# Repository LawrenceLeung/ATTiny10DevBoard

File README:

ATTiny10 in UDFN-6 dev board and HV programmer adapter for ICSP programmer

Designed for single layer etch process

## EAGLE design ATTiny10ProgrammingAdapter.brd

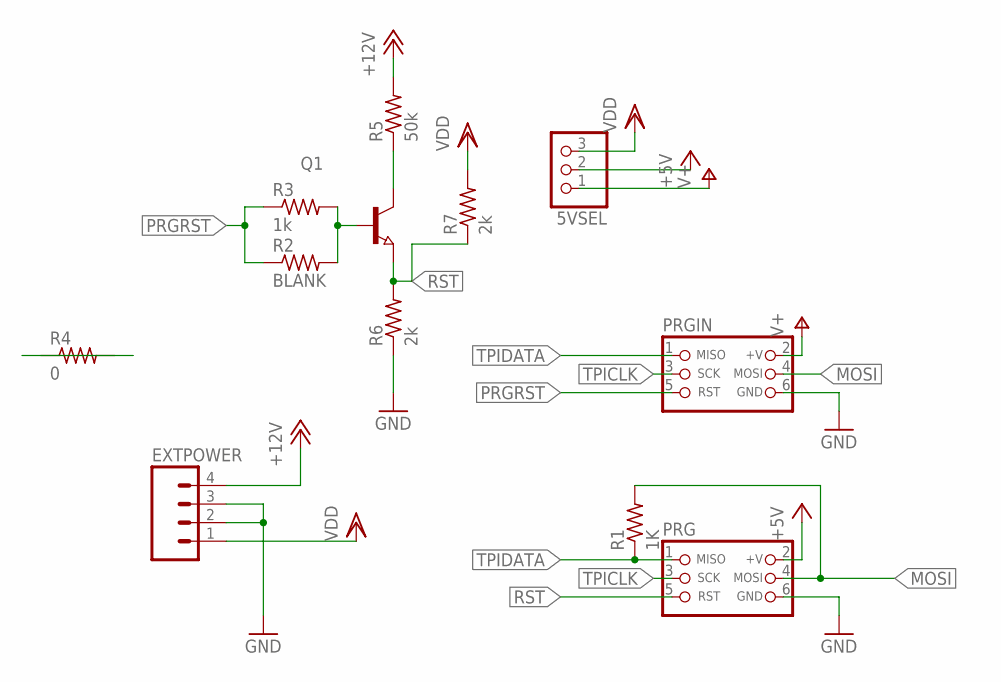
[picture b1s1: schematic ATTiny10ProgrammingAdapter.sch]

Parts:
5VSEL: PINHD-1X3CB; 1X03-CLEANBIG
EXTPOWER: HEADER1X4SMD_LONGPADS; 1X04-SMD-LONG
PRG: CON_HEADER_PRG_AVR_ICSP_ETCH; HEADER_PRG_2X03_ETCH
PRGIN: CON_HEADER_PRG_AVR_ICSP_ETCH; HEADER_PRG_2X03_ETCH
Q1: NPN-TRANSISTOR_SOT23; SOT23
R1: 1K; R0805
R2: BLANK; R0805
R3: 1k; R0805
R4: 0; R1206
R5: 50k; R0805
R6, R7: 2k; R0805

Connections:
+5V: 5VSEL.2, PRG.2 (+V)
+12V: EXTPOWER.4, R4.1, R4.2, R5.2
GND: EXTPOWER.2, EXTPOWER.3, PRG.6 (GND), PRGIN.6 (GND), R6.1
MOSI: PRG.4 (MOSI), PRGIN.4 (MOSI), R1.2
unnamed: Q1.1 (B), R2.2, R3.2
unnamed: Q1.3 (C), R5.1
PRGRST: PRGIN.5 (RST), R2.1, R3.1
RST: PRG.5 (RST), Q1.2 (E), R6.2, R7.1
TPICLK: PRG.3 (SCK), PRGIN.3 (SCK)
TPIDATA: PRG.1 (MISO), PRGIN.1 (MISO), R1.1
V+: 5VSEL.1, PRGIN.2 (+V)
VDD: 5VSEL.3, EXTPOWER.1, R7.2

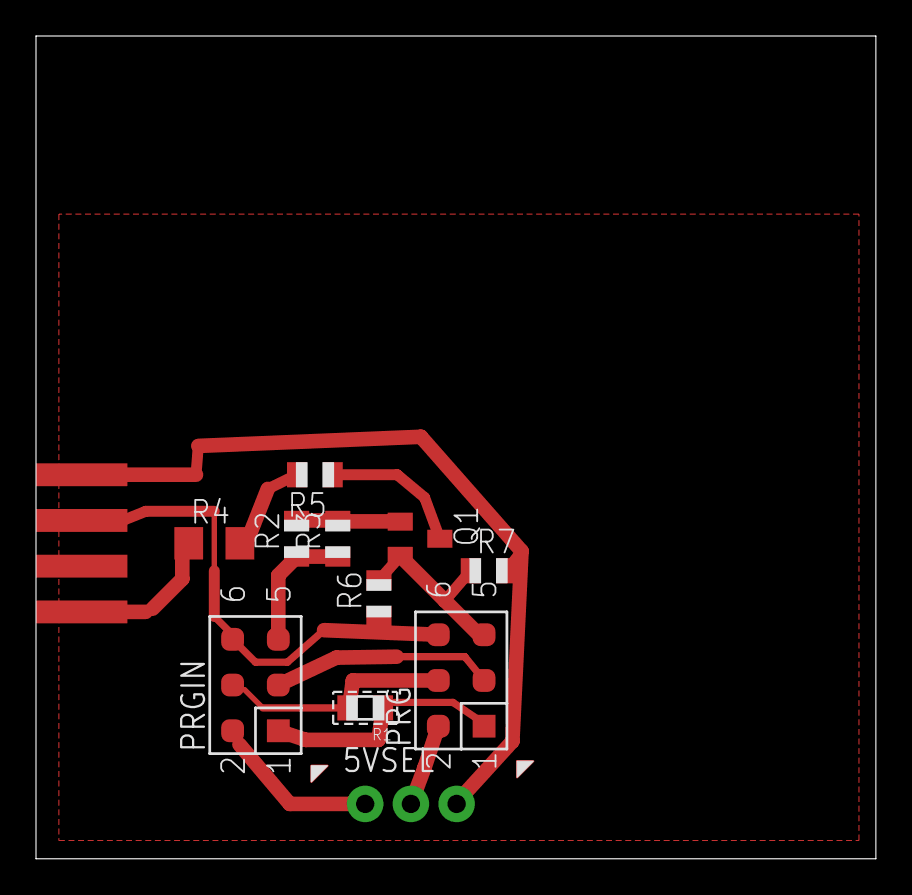
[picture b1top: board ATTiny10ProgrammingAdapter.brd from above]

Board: 2 copper layers, 46.7 x 45.7 mm, 12 parts (0 on the bottom side), 12 nets.

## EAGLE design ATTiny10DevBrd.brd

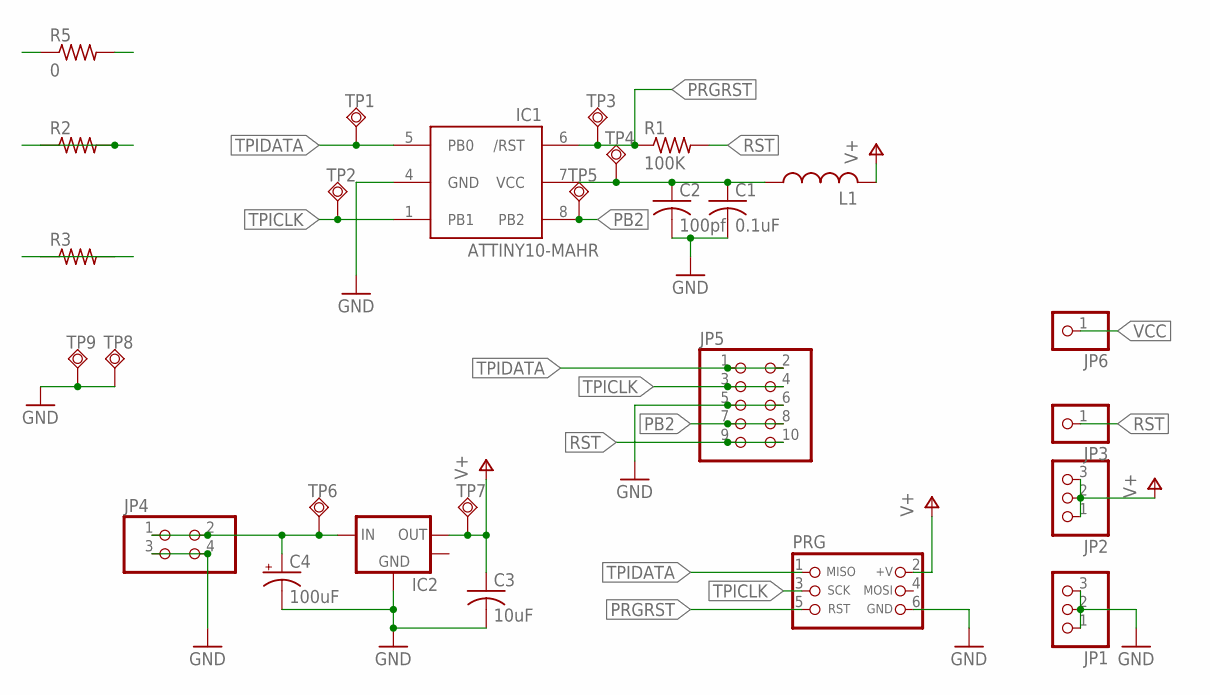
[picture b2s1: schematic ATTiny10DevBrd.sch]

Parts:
C1: 0.1uF; C0603
C2: 100pf; C0402
C3: 10uF; C0805K
C4: 100uF; PANASONIC_E
IC1: ATTINY10-MAHR; UDFN-8
IC2: V_REG_LM1117SOT223; SOT223
JP1, JP2: PINHD-1X3; 1X03
JP3, JP6: PINHD-1X1; 1X01
JP4: PINHD-2X2; 2X02
JP5: PINHD-2X5; 2X05
L1: L-USL1812; L1812
PRG: CON_HEADER_PRG_AVR_ICSP_ETCH; HEADER_PRG_2X03_ETCH
R1: 100K; R0805
R2, R3: R-US_M1206; M1206
R5: 0; M0805
TP1, TP2, TP3, TP4, TP5, TP6, TP7, TP8, TP9: TPSQTP12R; TP12R

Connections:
GND: C1.2, C2.2, C3.2, C4.-, IC1.4 (GND), IC2.1 (GND), JP1.1, JP1.2, JP1.3, JP4.3, JP4.4, JP5.5, JP5.6, PRG.6 (GND), TP8.TP, TP9.TP
PB2: IC1.8 (PB2), JP5.7, JP5.8, R3.1, R3.2, TP5.TP
PRGRST: IC1.6 (/RST), PRG.5 (RST), R1.1, TP3.TP
RST: JP3.1, JP5.9, JP5.10, R1.2
TPICLK: IC1.1 (PB1), JP5.3, JP5.4, PRG.3 (SCK), R2.1, R2.2, TP2.TP
TPIDATA: IC1.5 (PB0), JP5.1, JP5.2, PRG.1 (MISO), R5.1, R5.2, TP1.TP
V+: C3.1, IC2.2 (VR-OUTSM), JP2.1, JP2.2, JP2.3, L1.2, PRG.2 (+V), TP7.TP
VCC: C1.1, C2.1, IC1.7 (VCC), JP6.1, L1.1, TP4.TP
VIN: C4.+, IC2.3 (IN), JP4.1, JP4.2, TP6.TP

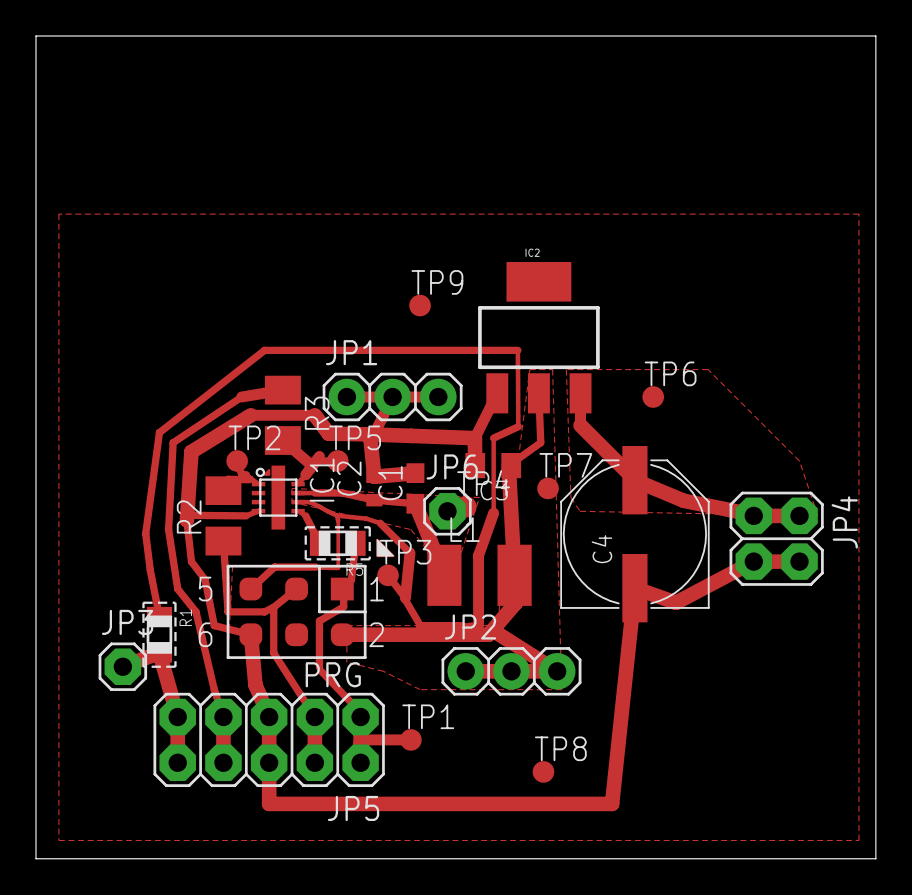
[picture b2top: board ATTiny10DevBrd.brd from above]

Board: 2 copper layers, 46.7 x 45.7 mm, 27 parts (0 on the bottom side), 9 nets.

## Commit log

2013-02-21 Initial ATTiny10 Dev board
2013-02-24 Dev board and programmer adapter
2013-02-24 Add readme
2013-02-24 add gitignore for cadsoft draft files
2013-02-24 Ignore autorouter state files
2013-02-25 Fix rest to default to pulldown when not active
2013-02-26 Tune traces
2013-03-10 Add reset pullup to VDD
2013-03-24 Tune up boards for printing
